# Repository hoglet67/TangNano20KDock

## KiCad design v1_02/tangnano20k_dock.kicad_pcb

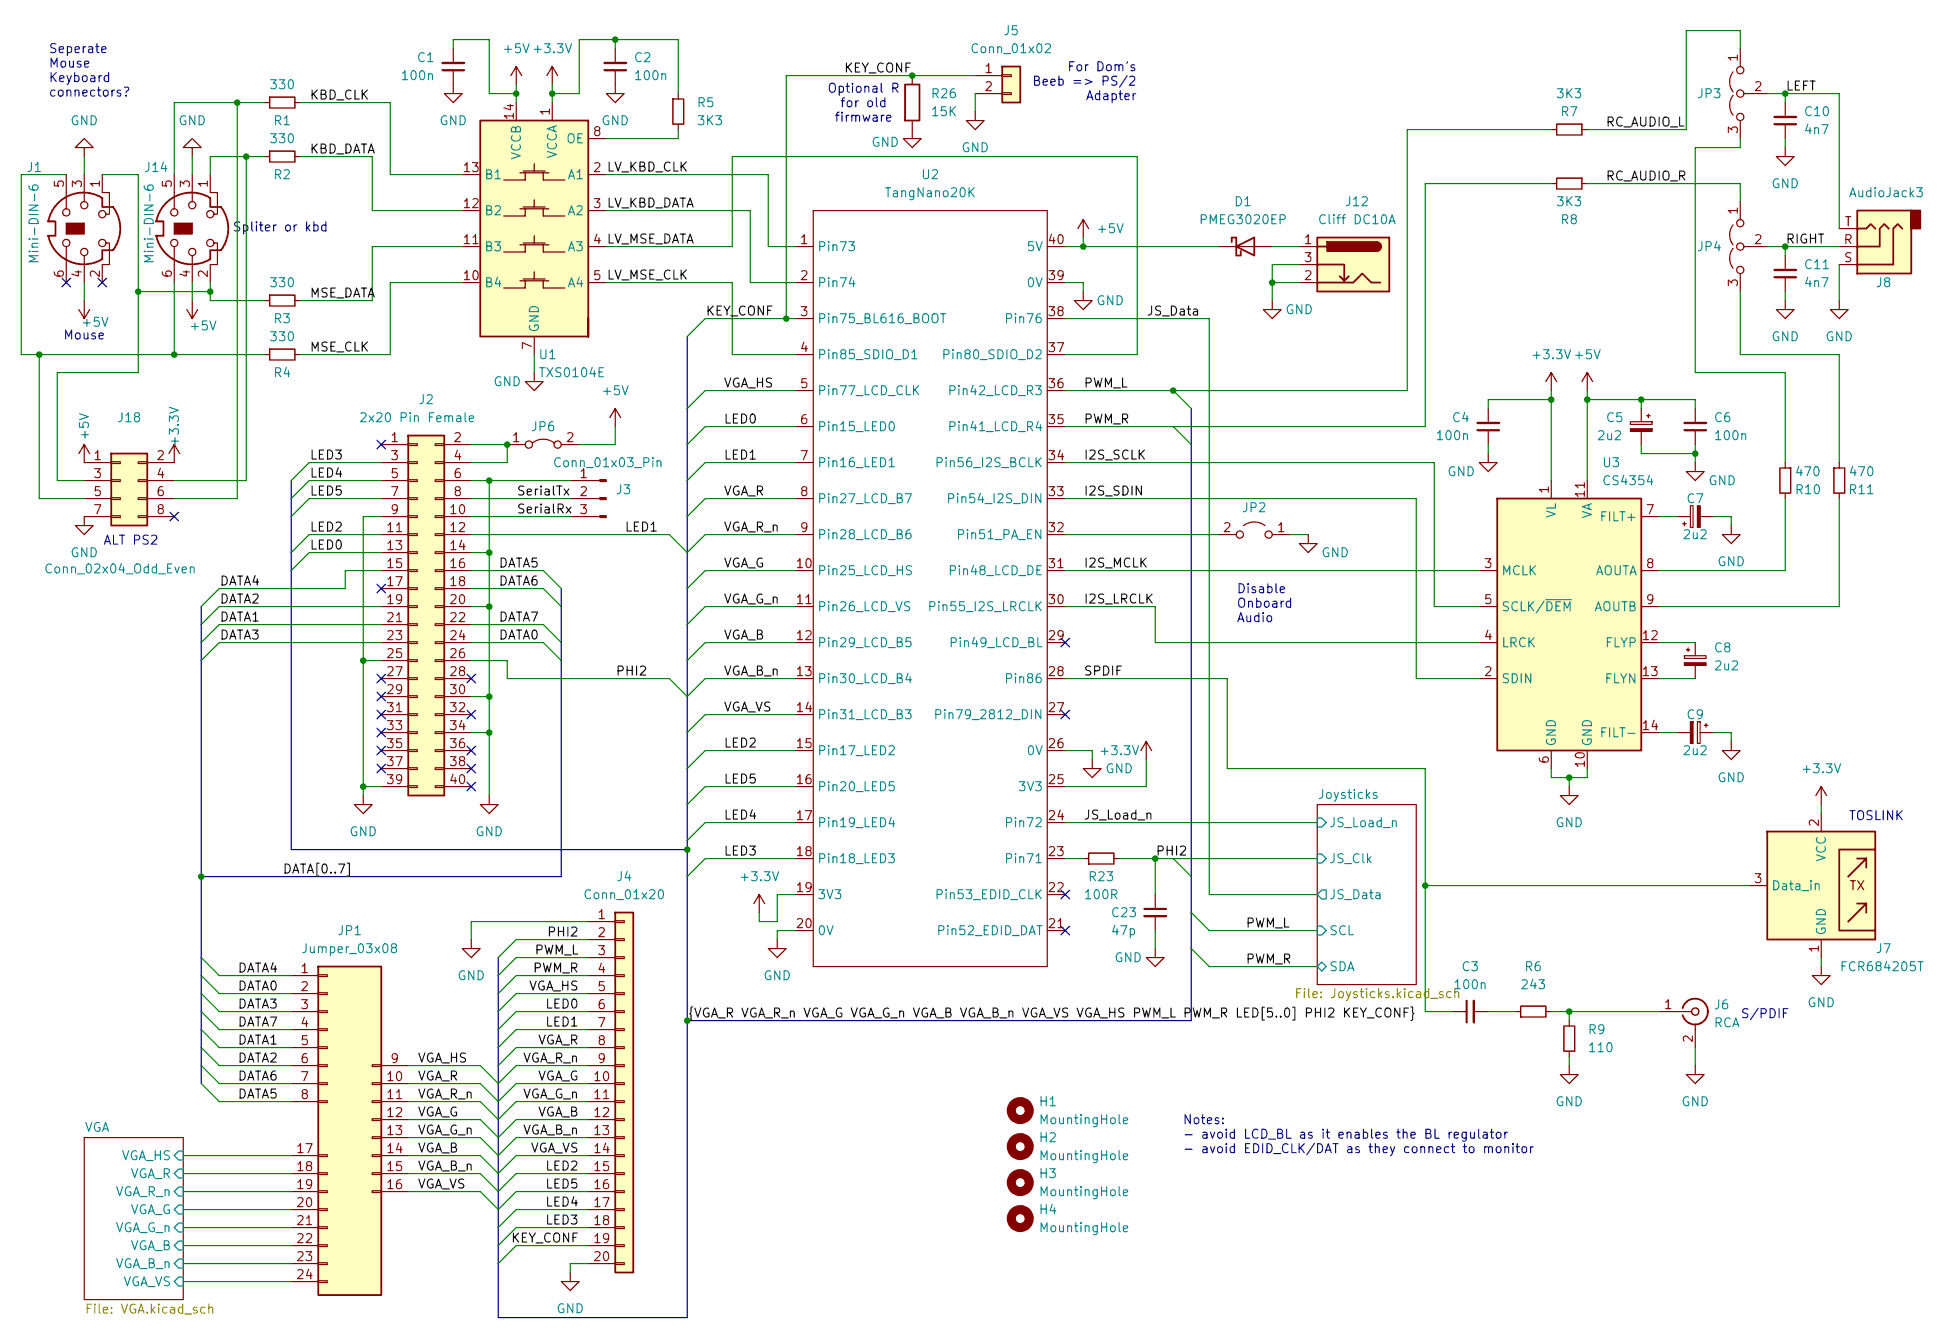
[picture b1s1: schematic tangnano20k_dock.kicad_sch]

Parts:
C1, C2, C3, C4, C6: 100n; C_1206_3216Metric_Pad1.33x1.80mm_HandSolder
C5, C7, C8, C9: 2u2; C_1206_3216Metric_Pad1.33x1.80mm_HandSolder
C10, C11: 4n7; C_1206_3216Metric_Pad1.33x1.80mm_HandSolder
C23: 47p; C_1206_3216Metric_Pad1.33x1.80mm_HandSolder
D1: PMEG3020EP; D_SOD-128
H1, H2, H3, H4: MountingHole; MountingHole_3.2mm_M3
J1, J14: Mini-DIN-6; minidin6
J2: 2x20 Pin Female; Raspberry_Pi_Zero_Socketed_THT_FaceDown_MountingHoles
J3: Conn_01x03_Pin; PinHeader_1x03_P2.54mm_Vertical
J4: Conn_01x20; PinHeader_1x20_P2.54mm_Vertical
J5: Conn_01x02; PinHeader_1x02_P2.54mm_Vertical
J6: RCA; phono
J7: FCR684205T
J8: AudioJack3; Jack_3.5mm_CUI_SJ1-3523N_Horizontal
J12: Cliff DC10A; CLIFF_FC68148_DC10A
J18: Conn_02x04_Odd_Even; IDC-Header_2x04_P2.54mm_Vertical
JP1: Jumper_03x08; PinHeader_3x08_P2.54mm_Vertical
JP2: Jumper_2_Open; PinHeader_1x02_P2.54mm_Vertical
JP3, JP4: Jumper_3_Open; PinHeader_1x03_P2.54mm_Vertical
JP6: Jumper_2_Bridged; PinHeader_1x02_P2.54mm_Vertical
R1, R2, R3, R4: 330; R_1206_3216Metric_Pad1.30x1.75mm_HandSolder
R5, R7, R8: 3K3; R_1206_3216Metric_Pad1.30x1.75mm_HandSolder
R6: 243; R_1206_3216Metric_Pad1.30x1.75mm_HandSolder
R9: 110; R_1206_3216Metric_Pad1.30x1.75mm_HandSolder
R10, R11: 470; R_1206_3216Metric_Pad1.30x1.75mm_HandSolder
R23: 100R; R_1206_3216Metric_Pad1.30x1.75mm_HandSolder
R26: 15K; R_1206_3216Metric_Pad1.30x1.75mm_HandSolder
U1: TXS0104E; SOIC-14_3.9x8.7mm_P1.27mm
U2: TangNano20K; TangNano20k
U3: CS4354; SOIC-14_3.9x8.7mm_P1.27mm

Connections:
+3.3V: C2.2, C4.2, J7.2 (VCC), J18.2, R5.1, U1.1 (VCCA), U2.19 (3V3), U2.25 (3V3), U3.1 (VL); also elsewhere on the board
+5V: C1.2, C5.1, C6.2, D1.1 (K), J1.4, J14.4, J18.1, JP6.2 (B), U1.14 (VCCB), U2.40 (5V), U3.11 (VA); also elsewhere on the board
/DATA0: J2.24, JP1.2
/DATA1: J2.21, JP1.5
/DATA2: J2.19, JP1.6
/DATA3: J2.23, JP1.3
/DATA4: J2.15, JP1.1
/DATA5: J2.16, JP1.8
/DATA6: J2.18, JP1.7
/DATA7: J2.22, JP1.4
/I2S_LRCLK: U2.30 (Pin55_I2S_LRCLK), U3.4 (LRCK)
/I2S_MCLK: U2.31 (Pin48_LCD_DE), U3.3 (MCLK)
/I2S_SCLK: U2.34 (Pin56_I2S_BCLK), U3.5 (SCLK/~DEM)
/I2S_SDIN: U2.33 (Pin54_I2S_DIN), U3.2 (SDIN)
/JS_Data: U2.38 (Pin76); also elsewhere on the board
/JS_Load_n: U2.24 (Pin72); also elsewhere on the board
/KBD_CLK: R1.2, U1.13 (B1)
/KBD_DATA: R2.2, U1.12 (B2)
/KEY_CONF: J4.19, J5.1, R26.1, U2.3 (Pin75_BL616_BOOT)
/LED0: J2.13, J4.6, U2.6 (Pin15_LED0)
/LED1: J2.12, J4.7, U2.7 (Pin16_LED1)
/LED2: J2.11, J4.15, U2.15 (Pin17_LED2)
/LED3: J2.3, J4.18, U2.18 (Pin18_LED3)
/LED4: J2.5, J4.17, U2.17 (Pin19_LED4)
/LED5: J2.7, J4.16, U2.16 (Pin20_LED5)
/LEFT: C10.2, J8.T, JP3.2 (C)
/LV_KBD_CLK: U1.2 (A1), U2.1 (Pin73)
/LV_KBD_DATA: U1.3 (A2), U2.2 (Pin74)
/LV_MSE_CLK: U1.5 (A4), U2.4 (Pin85_SDIO_D1)
/LV_MSE_DATA: U1.4 (A3), U2.37 (Pin80_SDIO_D2)
/MSE_CLK: R4.2, U1.10 (B4)
/MSE_DATA: R3.2, U1.11 (B3)
/PHI2: C23.1, J2.26, J4.2, R23.2; also elsewhere on the board
/PWM_L: J4.3, R7.2, U2.36 (Pin42_LCD_R3); also elsewhere on the board
/PWM_R: J4.4, R8.2, U2.35 (Pin41_LCD_R4); also elsewhere on the board
/RC_AUDIO_L: JP3.1 (A), R7.1
/RC_AUDIO_R: JP4.1 (A), R8.1
/RIGHT: C11.2, J8.R, JP4.2 (C)
/SPDIF: C3.1, J7.3 (Data_in), U2.28 (Pin86)
/SerialRx: J2.10, J3.3
/SerialTx: J2.8, J3.2
/VGA/VGA_B: JP1.22; also elsewhere on the board
/VGA/VGA_B_n: JP1.23; also elsewhere on the board
/VGA/VGA_G: JP1.20; also elsewhere on the board
/VGA/VGA_G_n: JP1.21; also elsewhere on the board
/VGA/VGA_HS: JP1.17; also elsewhere on the board
/VGA/VGA_R: JP1.18; also elsewhere on the board
/VGA/VGA_R_n: JP1.19; also elsewhere on the board
/VGA/VGA_VS: JP1.24; also elsewhere on the board
/VGA_B: J4.12, JP1.14, U2.12 (Pin29_LCD_B5)
/VGA_B_n: J4.13, JP1.15, U2.13 (Pin30_LCD_B4)
/VGA_G: J4.10, JP1.12, U2.10 (Pin25_LCD_HS)
/VGA_G_n: J4.11, JP1.13, U2.11 (Pin26_LCD_VS)
/VGA_HS: J4.5, JP1.9, U2.5 (Pin77_LCD_CLK)
/VGA_R: J4.8, JP1.10, U2.8 (Pin27_LCD_B7)
/VGA_R_n: J4.9, JP1.11, U2.9 (Pin28_LCD_B6)
/VGA_VS: J4.14, JP1.16, U2.14 (Pin31_LCD_B3)
GND: C1.1, C2.1, C4.1, C5.2, C6.1, C7.2, C9.1, C10.1, C11.1, C23.2, J1.3, J2.6, J2.9, J2.14, J2.20, J2.25, J2.30, J2.34, J2.39, J3.1, J4.1, J4.20, J5.2, J6.2 (Ext), J7.1 (GND), J8.S, J12.2, J12.3, J14.3, J18.7, JP2.1 (A), R9.1, R26.2, U1.7 (GND), U2.20 (0V), U2.26 (0V), U2.39 (0V), U3.6 (GND), U3.10 (GND); also elsewhere on the board
unnamed: C3.2, R6.1
unnamed: D1.2 (A), J12.1
unnamed: J2.2, J2.4, JP6.1 (A)
unnamed: J6.1 (In), R6.2, R9.2
unnamed: J1.1, J14.2, J18.3, R3.1
unnamed: J14.1, J18.4, R2.1
unnamed: J1.5, J14.6, J18.5, R4.1
unnamed: J14.5, J18.6, R1.1
unnamed: JP2.2 (B), U2.32 (Pin51_PA_EN)
unnamed: JP3.3 (B), R10.1
unnamed: JP4.3 (B), R11.1
unnamed: R5.2, U1.8 (OE)
unnamed: R23.1, U2.23 (Pin71)
unnamed: R10.2, U3.8 (AOUTA)
unnamed: R11.2, U3.9 (AOUTB)
unnamed: C7.1, U3.7 (FILT+)
unnamed: C9.2, U3.14 (FILT-)
unnamed: C8.2, U3.13 (FLYN)
unnamed: C8.1, U3.12 (FLYP)

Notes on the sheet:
Seperate Mouse Keyboard connectors?
TOSLINK
Optional R for old firmware
S/PDIF
Notes: - avoid LCD_BL as it enables the BL regulator - avoid EDID_CLK/DAT as they connect to monitor
Spliter or kbd
For Dom's Beeb => PS/2 Adapter
ALT PS2
Mouse
Disable Onboard Audio

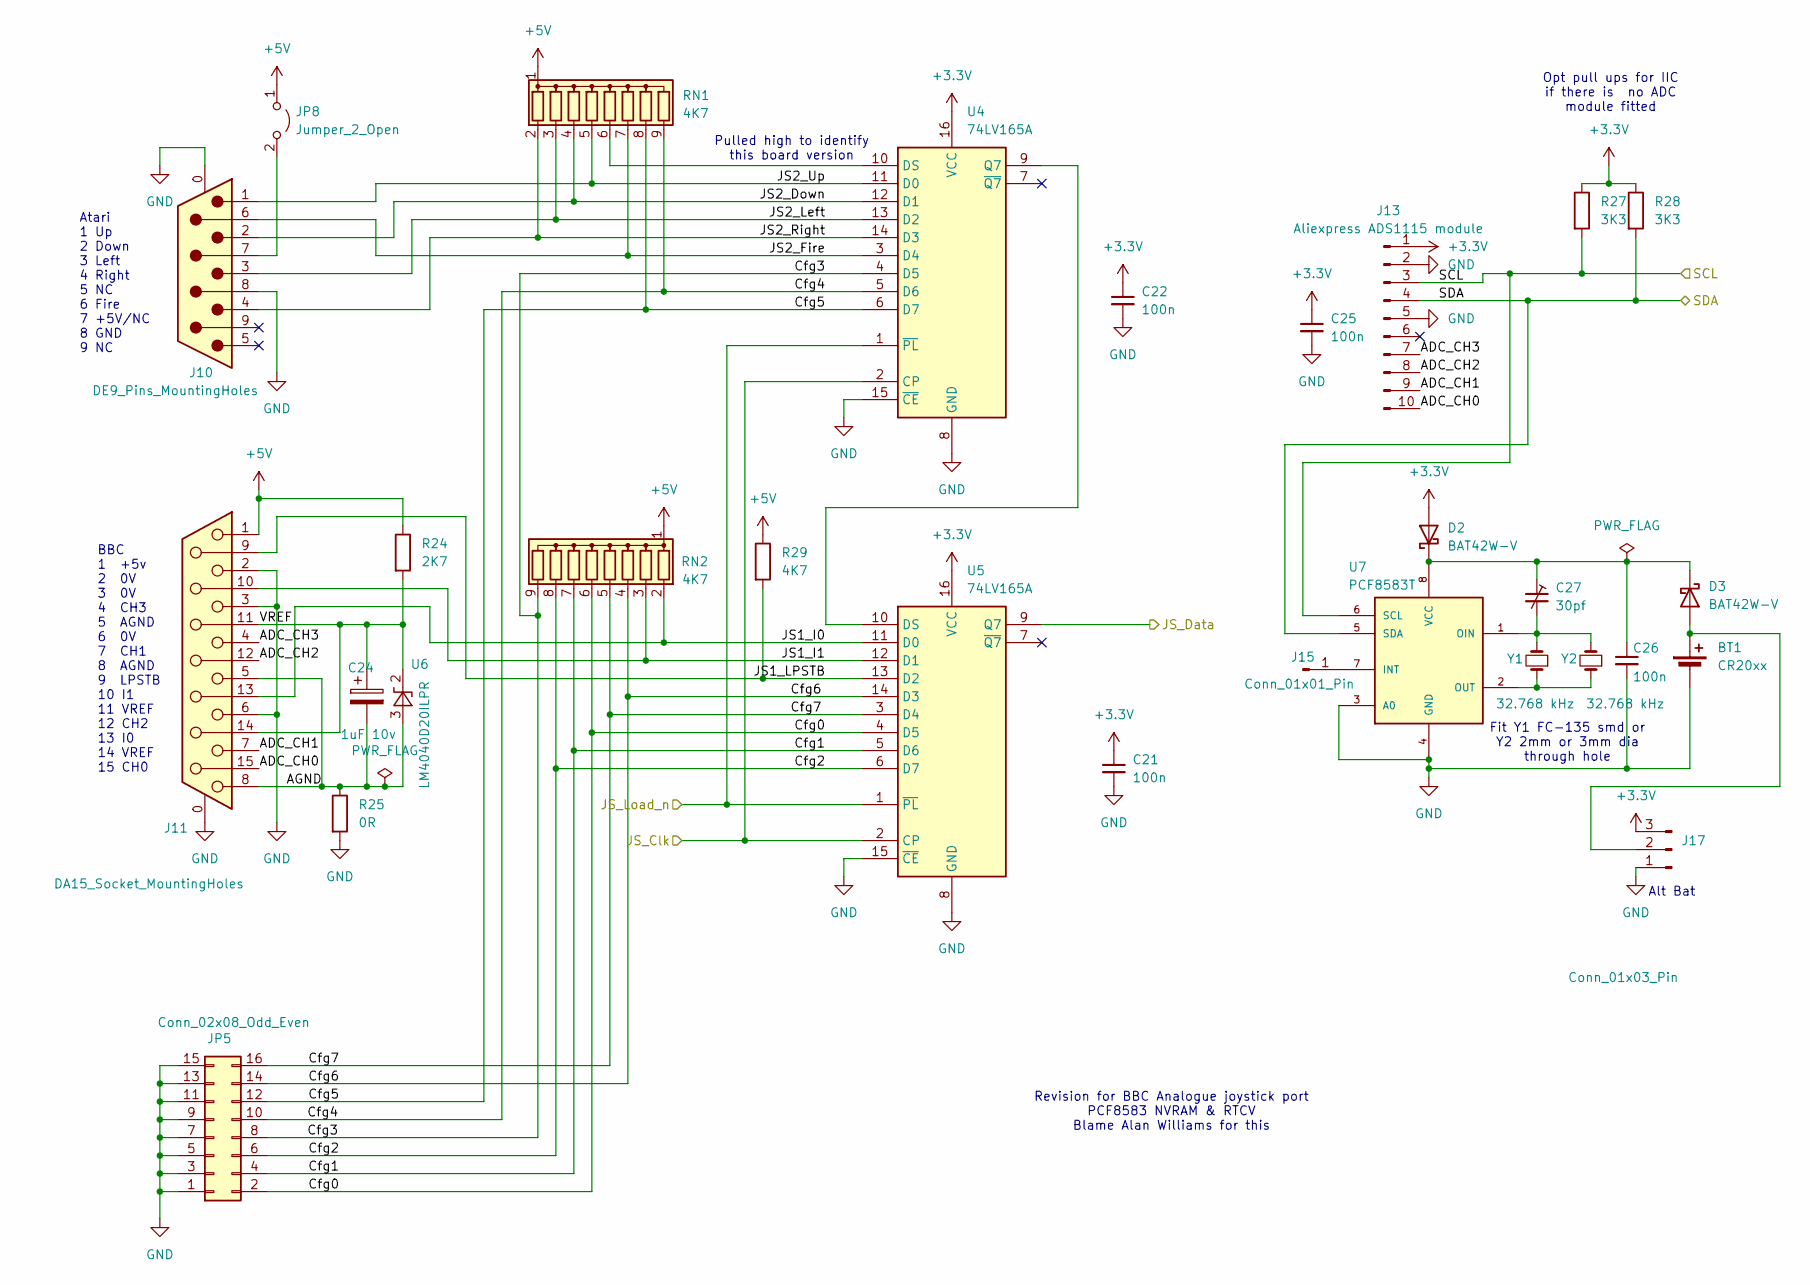
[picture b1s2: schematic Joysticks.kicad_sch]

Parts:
BT1: CR20xx; BatteryHolder_Keystone_103_1x20mm
C21, C22, C25, C26: 100n; C_1206_3216Metric_Pad1.33x1.80mm_HandSolder
C24: 1uF 10v; C_1206_3216Metric_Pad1.33x1.80mm_HandSolder
C27: 30pf; C_Trimmer_Murata_TZB4-B
D2, D3: BAT42W-V; D_SOD-123
J10: DE9_Pins_MountingHoles; DSUB-9_Pins_Horizontal_P2.77x2.84mm_EdgePinOffset7.70mm_Hou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
J11: DA15_Socket_MountingHoles; DSUB-15_Socket_Horizontal_P2.77x2.84mm_EdgePinOffset7.70mm_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
J13: Aliexpress ADS1115 module; PinHeader_1x10_P2.54mm_Vertical
J15: Conn_01x01_Pin; PinHeader_1x01_P2.54mm_Vertical
J17: Conn_01x03_Pin; PinHeader_1x03_P2.54mm_Horizontal
JP5: Conn_02x08_Odd_Even; PinHeader_2x08_P2.54mm_Vertical
JP8: Jumper_2_Open; PinHeader_1x02_P2.54mm_Vertical
R24: 2K7; R_1206_3216Metric_Pad1.30x1.75mm_HandSolder
R25: 0R; R_1206_3216Metric_Pad1.30x1.75mm_HandSolder
R27, R28: 3K3; R_1206_3216Metric_Pad1.30x1.75mm_HandSolder
R29: 4K7; R_1206_3216Metric_Pad1.30x1.75mm_HandSolder
RN1, RN2: 4K7; R_Array_SIP9
U4, U5: 74LV165A; SOIC-16_3.9x9.9mm_P1.27mm
U6: LM4040D20ILPR; TO-92_HandSolder
U7: PCF8583T; SOIC-8_7.5x5.85mm_P1.27mm
Y1: 32.768 kHz; Crystal_SMD_3215-2Pin_3.2x1.5mm
Y2: 32.768 kHz; Crystal_Round_D3.0mm_Vertical

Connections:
+3.3V: C21.1, C22.1, C25.1, D2.2 (A), J13.1, J17.3, R27.1, R28.1, U4.16 (VCC), U5.16 (VCC); also elsewhere on the board
+5V: J11.1, JP8.1 (A), R24.1, R29.1, RN1.1 (common), RN2.1 (common); also elsewhere on the board
/JS_Data: U5.9 (Q7); also elsewhere on the board
/JS_Load_n: U4.1 (~PL), U5.1 (~PL); also elsewhere on the board
/Joysticks/ADC_CH0: J11.15, J13.10
/Joysticks/ADC_CH1: J11.7, J13.9
/Joysticks/ADC_CH2: J11.12, J13.8
/Joysticks/ADC_CH3: J11.4, J13.7
/Joysticks/AGND: C24.2, J11.5, J11.8, R25.1, U6.3 (A)
/Joysticks/Cfg0: JP5.2, RN2.6 (R5), U5.4 (D5)
/Joysticks/Cfg1: JP5.4, RN2.7 (R6), U5.5 (D6)
/Joysticks/Cfg2: JP5.6, RN2.8 (R7), U5.6 (D7)
/Joysticks/Cfg3: JP5.8, RN2.9 (R8), U4.4 (D5)
/Joysticks/Cfg4: JP5.10, RN1.9 (R8), U4.5 (D6)
/Joysticks/Cfg5: JP5.12, RN1.8 (R7), U4.6 (D7)
/Joysticks/Cfg6: JP5.14, RN2.4 (R3), U5.14 (D3)
/Joysticks/Cfg7: JP5.16, RN2.5 (R4), U5.3 (D4)
/Joysticks/JS1_I0: J11.13, RN2.2 (R1), U5.11 (D0)
/Joysticks/JS1_I1: J11.10, RN2.3 (R2), U5.12 (D1)
/Joysticks/JS1_LPSTB: J11.9, R29.2, U5.13 (D2)
/Joysticks/JS2_Down: J10.2, RN1.4 (R3), U4.12 (D1)
/Joysticks/JS2_Fire: J10.6, RN1.7 (R6), U4.3 (D4)
/Joysticks/JS2_Left: J10.3, RN1.3 (R2), U4.13 (D2)
/Joysticks/JS2_Right: J10.4, RN1.2 (R1), U4.14 (D3)
/Joysticks/JS2_Up: J10.1, RN1.5 (R4), U4.11 (D0)
/Joysticks/VREF: C24.1, J11.11 (P111), J11.14, R24.2, U6.2 (K)
/PHI2: U4.2 (CP), U5.2 (CP); also elsewhere on the board
/PWM_L: J13.3, R27.2, U7.6 (SCL); also elsewhere on the board
/PWM_R: J13.4, R28.2, U7.5 (SDA); also elsewhere on the board
GND: BT1.2 (-), C21.2, C22.2, C25.2, C26.2, J10.0 (PAD), J10.8, J11.0 (PAD), J11.2, J11.3, J11.6, J13.2, J13.5, J17.1, JP5.1, JP5.3, JP5.5, JP5.7, JP5.9, JP5.11, JP5.13, JP5.15, R25.2, U4.8 (GND), U4.15 (~CE), U5.8 (GND), U5.15 (~CE), U7.3 (A0), U7.4 (GND); also elsewhere on the board
unnamed: BT1.1 (+), D3.2 (A), J17.2
unnamed: C26.1, C27.1, D2.1 (K), D3.1 (K), U7.8 (VCC)
unnamed: J15.1, U7.7 (INT)
unnamed: J10.7, JP8.2 (B)
unnamed: RN1.6 (R5), U4.10 (DS)
unnamed: U4.9 (Q7), U5.10 (DS)
unnamed: C27.2, U7.1 (OIN), Y1.2, Y2.2
unnamed: U7.2 (OUT), Y1.1, Y2.1

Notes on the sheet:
Opt pull ups for IIC if there is no ADC module fitted
Atari 1 Up 2 Down 3 Left 4 Right 5 NC 6 Fire 7 +5V/NC 8 GND 9 NC
Alt Bat
Fit Y1 FC-135 smd or Y2 2mm or 3mm dia through hole
Pulled high to identify this board version
BBC 1 +5v 2 0V 3 0V 4 CH3 5 AGND 6 0V 7 CH1 8 AGND 9 LPSTB 10 I1 11 VREF 12 CH2 13 I0 14 VREF 15 CH0
Revision for BBC Analogue joystick port PCF8583 NVRAM & RTCV Blame Alan Williams for this

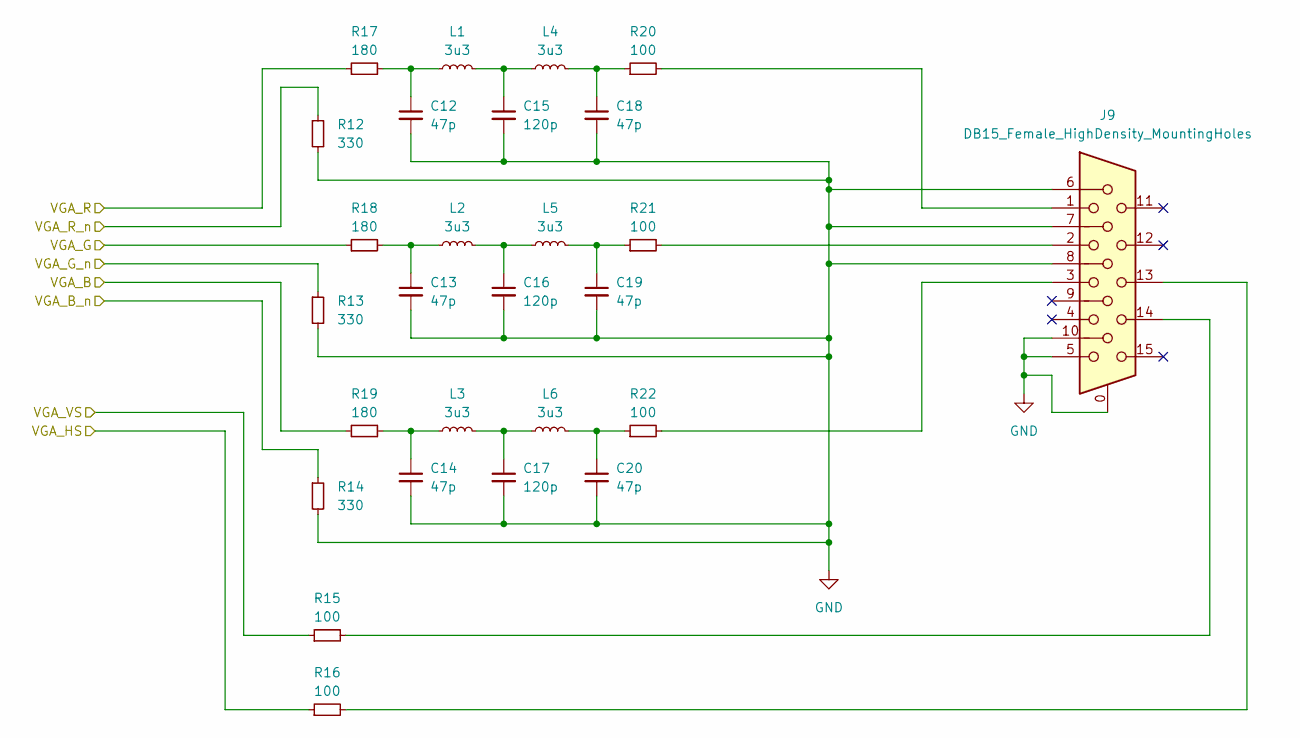
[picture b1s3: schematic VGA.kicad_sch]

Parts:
C12, C13, C14, C18, C19, C20: 47p; C_1206_3216Metric_Pad1.33x1.80mm_HandSolder
C15, C16, C17: 120p; C_1206_3216Metric_Pad1.33x1.80mm_HandSolder
J9: DB15_Female_HighDensity_MountingHoles; DSUB-15-HD_Female_Horizontal_P2.29x1.98mm_EdgePinOffset8.35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
L1, L2, L3, L4, L5, L6: 3u3; L_1206_3216Metric_Pad1.22x1.90mm_HandSolder
R12, R13, R14: 330; R_1206_3216Metric_Pad1.30x1.75mm_HandSolder
R15, R16, R20, R21, R22: 100; R_1206_3216Metric_Pad1.30x1.75mm_HandSolder
R17, R18, R19: 180; R_1206_3216Metric_Pad1.30x1.75mm_HandSolder

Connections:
/VGA/VGA_B: R19.1; also elsewhere on the board
/VGA/VGA_B_n: R14.1; also elsewhere on the board
/VGA/VGA_G: R18.1; also elsewhere on the board
/VGA/VGA_G_n: R13.1; also elsewhere on the board
/VGA/VGA_HS: R16.1; also elsewhere on the board
/VGA/VGA_R: R17.1; also elsewhere on the board
/VGA/VGA_R_n: R12.1; also elsewhere on the board
/VGA/VGA_VS: R15.1; also elsewhere on the board
GND: C12.2, C13.2, C14.2, C15.2, C16.2, C17.2, C18.2, C19.2, C20.2, J9.0, J9.5, J9.6, J9.7, J9.8, J9.10, R12.2, R13.2, R14.2; also elsewhere on the board
unnamed: C12.1, L1.1, R17.2
unnamed: C13.1, L2.1, R18.2
unnamed: C14.1, L3.1, R19.2
unnamed: C15.1, L1.2, L4.1
unnamed: C16.1, L2.2, L5.1
unnamed: C17.1, L3.2, L6.1
unnamed: C18.1, L4.2, R20.1
unnamed: C19.1, L5.2, R21.1
unnamed: C20.1, L6.2, R22.1
unnamed: J9.1, R20.2
unnamed: J9.2, R21.2
unnamed: J9.3, R22.2
unnamed: J9.13, R16.2
unnamed: J9.14, R15.2

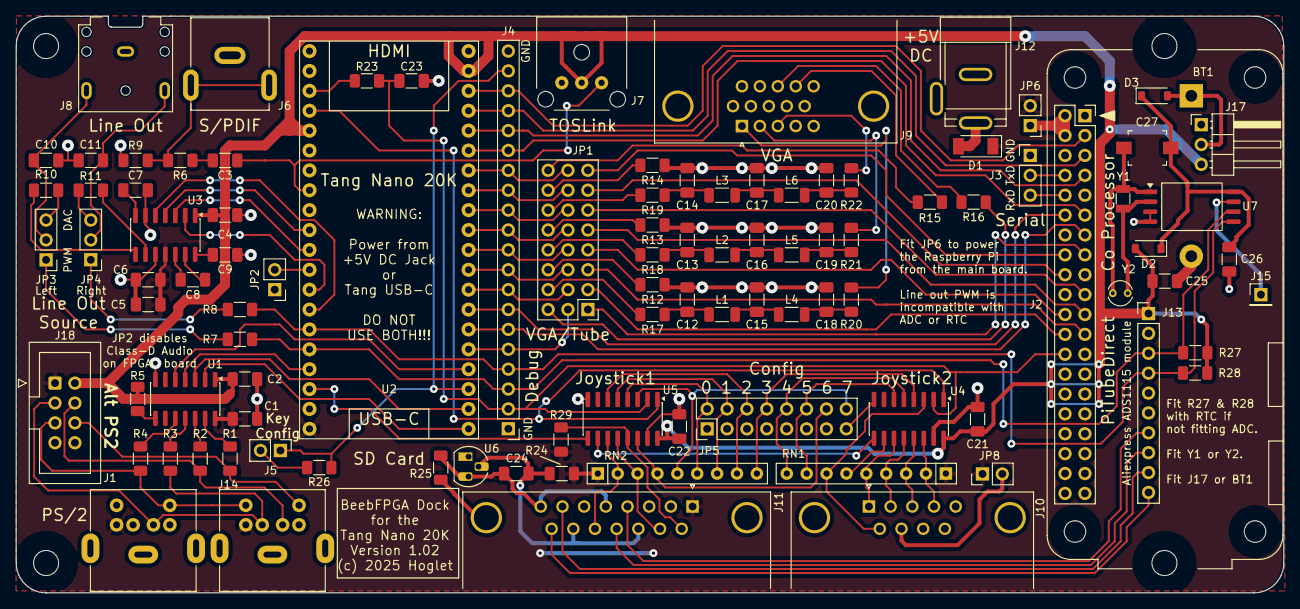
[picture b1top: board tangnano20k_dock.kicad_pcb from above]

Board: 2 copper layers, 161.9 x 73.7 mm, 105 parts (1 on the bottom side), 121 nets.

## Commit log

2025-02-22 Everything connected
2025-02-23 Much tidying up, corrected VGA footprint
2025-02-23 Corrected Joystick footprint
2025-02-23 Re-orient resistors
2025-02-24 Silk screen only
2025-02-24 Refresh PDF schematic
2025-04-26 Minor changes
2025-04-26 Start again, using 1206 SMT
2025-04-27 Work in progress
2025-04-27 Fully routed and passes DRC
2025-04-27 Silk screen
2025-04-28 Added rounded corners
2025-04-28 Updated VGA jumper block from 2x6 to 3x6
2025-04-28 Updated VGA jumper block from 3x6 to 3x8
2025-04-28 Spread out VGA filter passives
2025-04-28 Spread out audio passives
2025-04-28 Corrected error in PS/2 footprint
2025-04-28 Refresh PDF
2025-04-28 Silk-screen and swap PWM L/R labels
2025-04-28 Added jumpers for Pi and Joystick power
2025-04-29 Hacked in some 3D models for custom footprints
2025-04-29 Switched to Cliffe FC68131 Jack (matches CUI_SJ1-3523N footprint)
2025-04-29 Add 3D model for 3.5mm Jack
2025-04-29 Switched to Pro Signal PSG01547 for Phono
2025-04-29 Added optional mounting holes for phono
2025-04-29 Add 3D model for FCR684205T optical transmitter
2025-04-29 Extend board to allow mounting holes for Raspberry Pi
2025-04-29 Make mounting holes orthogonal
2025-04-29 Tweaked power routing around Pi
2025-04-29 Move R15/16 a bit
2025-04-29 Tidy around Joystick connectors
2025-04-29 Nudge J4 and JP1 over slightly
2025-04-29 Add clearance around mounting holes
2025-04-29 Add 2x20 3D model to Pi footprint
2025-04-30 Drive PiTube PHI2 from WS2812 output, freeing up PWM
2025-04-30 Correct swapped net names LED3 and LED5
2025-04-30 Add KEY_CONF to DEBUG header
2025-04-30 Drive PiTube PHI2 from js_clk to save a pin
2025-04-30 Add an RC filter to allow PHI2 clock edge to be slowed to avoid ringing
2025-05-01 Added Cliff DC10A power jack + schottky diode
2025-05-01 Beef up longer 5V tracks
2025-05-01 Added 3D model for SOD128 diode
2025-05-01 Address some DFM issues
2025-05-01 More minor DFM issues
2025-05-01 Re-layout VGA filter + used 5V plane
2025-05-01 Tweak routing around +5V into Nano
2025-05-01 Double up on the VGA filter GND vias
2025-05-01 Added manufacturing files
2025-05-04 Update resistor values and refresh PDF
2025-05-15 Added SMT Passive assembly notes
2025-05-15 Added errara for v1.00 PCB
2025-05-16 Updated errara for v1.00 PCB
2025-06-08 Update Errata
2025-12-20 Added v1.01 files from awilliams
2025-12-20 Made a copy of v1_01 as v1_02 to address ERC/DRC warnings etc
2025-12-20 v1_02: Fix some ERC warnings
2025-12-20 v1_02: Updated symbols/footprints for KiCAD9; fix all ERC/DRC warnings
2025-12-20 Refresh v1_01 PDF schematic
2025-12-20 Refresh v1_02 PDF schematic
2025-12-23 Started errata for v1.01
2025-12-23 v1_02: Increase PS/2 + Tang hole sizes; corrected U6 symbol
2025-12-23 v1_02: Removed NPTH holes from Photo footprint
2026-01-07 Updated errata for v1.01

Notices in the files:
v1_02/tangnano20k_dock.kicad_pcb:
(c) 2025 Hoglet
